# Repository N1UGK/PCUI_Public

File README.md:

# PCUI (Pocket Computer Universal Interface)
This is the official repo for firmware updates for the PCUI, owners manuals, and general information.  Further, this repo contains a collection of programs for various pocket computers and calculators supported by the PCUI.

## Development History

https://n1ugk.com/2025/12/pocket-computer-universal-interface/

## Features Summary

+ Provides cassette interface emulation to read and write programs and data directly to and from a micro SD card.
+ Provides a printer interface between the pocket computer or calculator and most standard “line printers” such as dot matrix, thermal receipt printers, serial, parallel, and Wi-Fi.
+ Supports printing of custom glyphs, including math, scientific and engineering symbols unique to each model.
+ Works independently without a computer and can be powered by a single 18650 lithium ion rechargeable battery.
+ OLED screen with user-friendly menu system and operating modes
+ Interface packs provide connectivity to each supported model, no need for OEM connection cables.
+ Updatable firmware and PC or Mac connectivity via USB for mounting micro SD card
+ Plotter emulation mode to provide printouts of plots using modern printers allowing programs which leveraged plotter features to be used on modern printers.
+ ASCII BASIC conversion to tokenized BASIC “on the fly”, allowing for program edits and program creation on a Mac or PC and directly sending it to a pocket computer.
+ Wi-Fi connectivity and web interface for program viewing, editing, UI control, printing, and status.
+ Online program library browsing and installing directly from GitHub allows you to view community released programs for various models of pocket computers directly from the PCUI.
+ True low-level cassette interface integration - byte level retrieval and storage of programs and data images, not just a simple "record" and "playback" mechanism.
+	3D printed case available with additional “docking station” 3D models for specific pocket computers.
  
## Supported Models

The following models are currently supported with more models in progress:

+ Texas Instruments	Graph Link Graphing Calculators
  + TI-82*, TI-85*, TI-86*, TI-89*, TI-92*, TI-92 Plus*, Voyage 200*
+ Sharp 9-pin “CE-121” / “CE-122” Compatibles
  + PC-1210, PC-1211, PC-1212, TRS-80 PC-1*
+ Sharp	Older 11-pin “CE-126P” Compatibles
  + PC-1245, PC-1246, PC-1246S, PC-1247, PC-1248, Tandy PC-8*
  + PC-1250, PC-1250A, PC-1251, PC-1251H, PC-1255, Tandy PC-3* and PC-3 A/B*, PC-1270
+ 11-pin “CE-126P” Compatibles
  + PC-1260, PC-1280
+ Sharp	Newer 11-pin “CE-126P” Compatibles
  + PC-1401, PC-1403*, PC-1421, PC-1430, PC-1450, EL-5500, EL-5500 II, EL-5500III*
+ Casio	12-pin PB-100 Series FP-12(S) Compatibles
  + PB-100, PB-110, PB-120, PB-200, PB-400, PB-410*, FX-700P, FX-710P, Tandy PC-4 Version B*, TRS-80 PC-4 Version A*
+ Casio	12-pin FX “Clamshell” Series
  + FX-770P, FX-780P, FX-781P, FX-785P, FX-790P, FX-791P, FX-795P, Tandy PC-5*, Tandy PC-6*
+ Casio	15-pin “FA-10” Compatibles
  + PB-700*, PB-770*
+ Casio	FX-702P*, FX-602P*

_*Tested and Verified, others should work since they use the same interface_

The PCUI Owners manual can be found in the [Documentation](./Documentation/) folder.

Firmware updates can be found in the [Firmware](./Firmware/) folder.

## 3D Printed Case

The PCUI has a case which can printed with a 3D printer.  The case STEP files are in the hardware folder.  The case includes all 3D models needed - both the top and bottom halves of the case, the 4 buttons, the two pocket computer connector covers, and the slide switch.

In addition to the PCUI case, there will be several "docking station" style model files as well.  For example, there is a TRS-80 PC-4 / Casio PB-100 series dock available for printing.  The interface pack fits inside of the 3D printed dock, providing a stable platform for connecting the pocket computer to the PCUI.  Similar models will be created for other pocket computers and made available as well.

## 3D Printed "Docks"

Several interface packs have optional "docks" available for providing a more stable connection and better usability.  These are 3D printed and also available here under the Hardware folder if you wish to print them yourself.

## Purchasing a Kit or Fully Assembled PCUI

A PCUI can be purchased as a kit or fully assembled.  

+ PCUI Kit - includes pre-flashed Pico 2 W, Main PCB and all components.  Interface pack kits are add-ons.  
  + Assembly instructions are located in the [Documentation](./Documentation/) folder.
  + The BOM, 3D model, KiCad Projects are located in the [Hardware](./Hardware/) folder.
+ PCUI Fully Assembled - includes a fully assembled PCUI and chosen interface pack add-ons.
+ To purchase a PCUI, <a href="https://www.tindie.com/products/n1ugk/pocket-computer-universal-interface-pcui/">click here</a>.

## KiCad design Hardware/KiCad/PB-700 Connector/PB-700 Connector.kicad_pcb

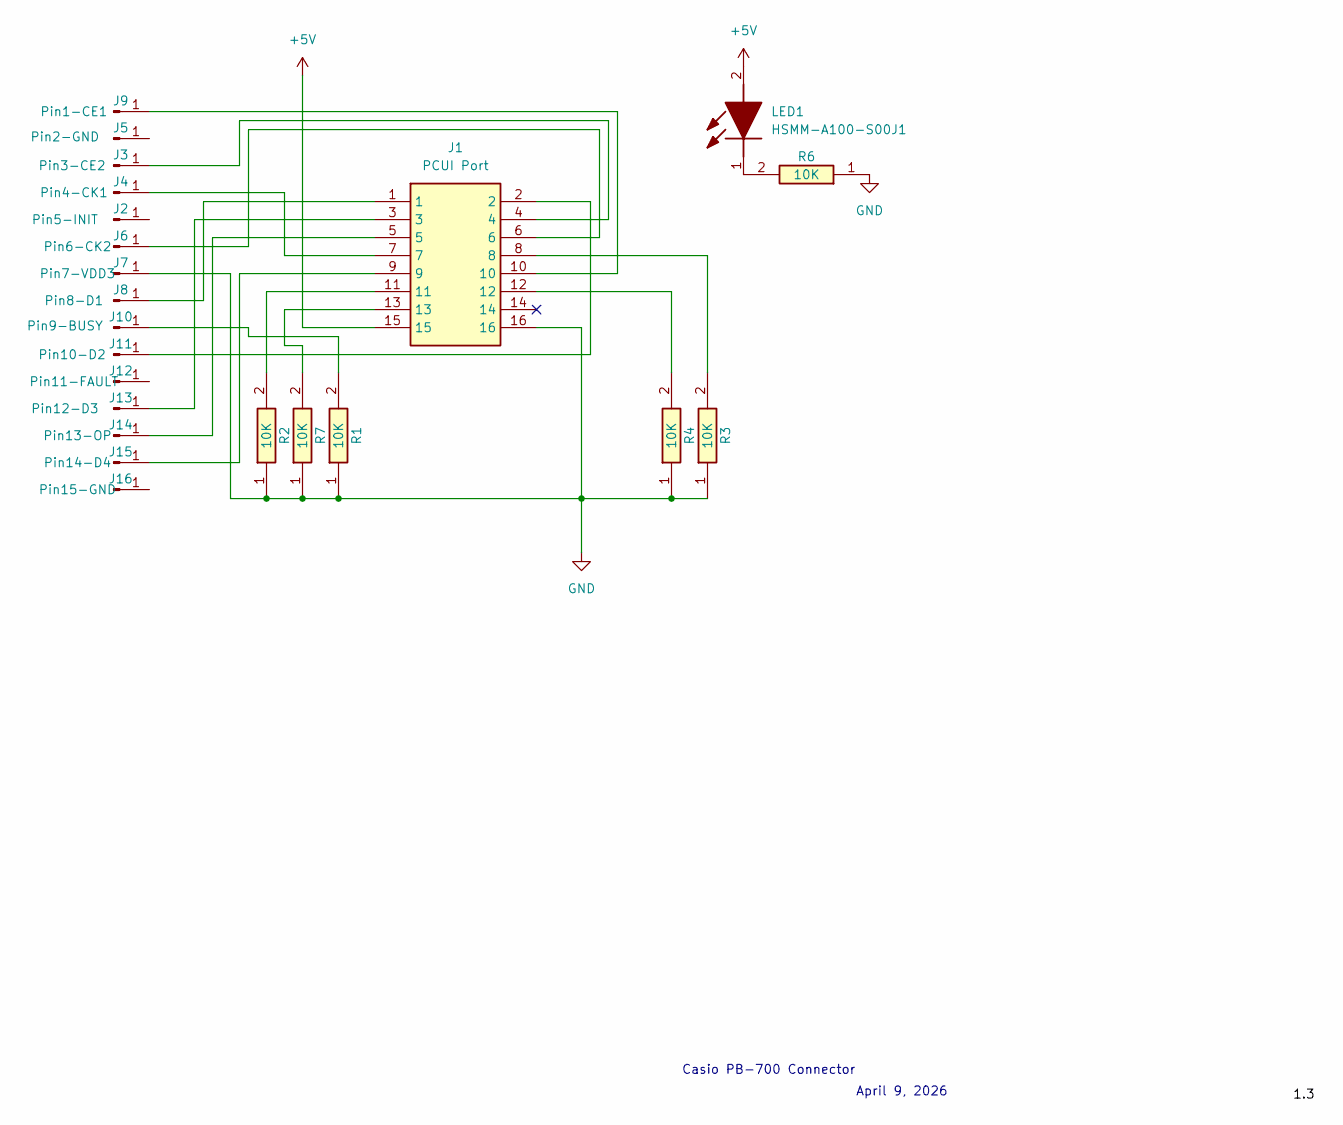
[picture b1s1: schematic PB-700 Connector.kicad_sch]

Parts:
J1: PCUI Port; TSS-108-XX-YYY-D; Manufacturer_Part_Number TSS-108-02-L-D
J2: Pin5-INIT; TH_1mm_1.5mm
J3: Pin3-CE2; TH_1mm_1.5mm
J4: Pin4-CK1; TH_1mm_1.5mm
J5: Pin2-GND; TH_1mm_1.5mm
J6: Pin6-CK2; TH_1mm_1.5mm
J7: Pin7-VDD3; TH_1mm_1.5mm
J8: Pin8-D1; TH_1mm_1.5mm
J9: Pin1-CE1; TH_1mm_1.5mm
J10: Pin9-BUSY; TH_1mm_1.5mm
J11: Pin10-D2; TH_1mm_1.5mm
J12: Pin11-FAULT; TH_1mm_1.5mm
J13: Pin12-D3; TH_1mm_1.5mm
J14: Pin13-OP; TH_1mm_1.5mm
J15: Pin14-D4; TH_1mm_1.5mm
J16: Pin15-GND; TH_1mm_1.5mm
LED1: HSMM-A100-S00J1; LEDM3528X200N; Mouser Part Number 630-HSMM-A100-S00J1
R1, R2, R3, R4, R6, R7: 10K; RESC2013X65N; Mouser Part Number 756-WCR0805-10KFI

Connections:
+5V: J1.15, LED1.2 (A)
GND: J1.16, J7.1, R1.1, R2.1, R3.1, R4.1, R6.1, R7.1
unnamed: J1.8, R3.2
unnamed: J1.11, R2.2
unnamed: J1.12, R4.2
unnamed: J1.13, R7.2
unnamed: J1.4, J3.1
unnamed: J1.7, J4.1
unnamed: J1.6, J6.1
unnamed: J1.1, J8.1
unnamed: J1.10, J9.1
unnamed: J10.1, R1.2
unnamed: J1.2, J11.1
unnamed: J1.3, J13.1
unnamed: J1.5, J14.1
unnamed: J1.9, J15.1
unnamed: LED1.1 (K), R6.2

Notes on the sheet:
April 9, 2026
Casio PB-700 Connector

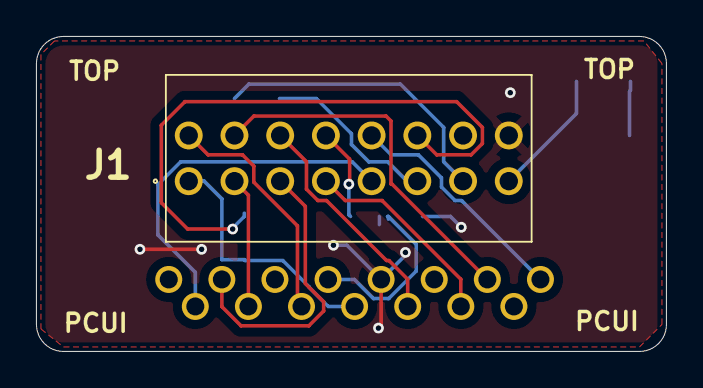
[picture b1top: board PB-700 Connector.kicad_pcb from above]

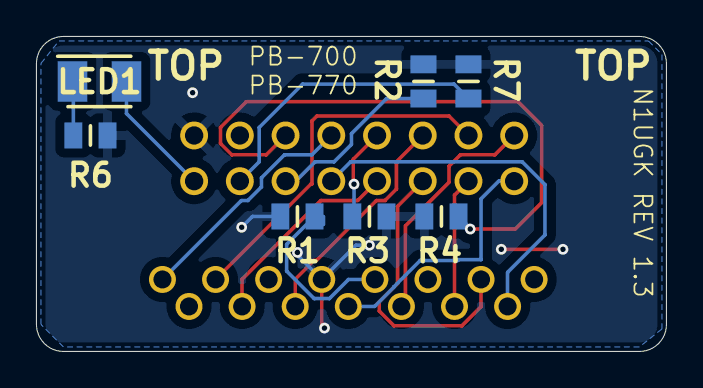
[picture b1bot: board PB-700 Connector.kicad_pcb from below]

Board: 2 copper layers, 35.0 x 17.5 mm, 23 parts (22 on the bottom side), 17 nets.

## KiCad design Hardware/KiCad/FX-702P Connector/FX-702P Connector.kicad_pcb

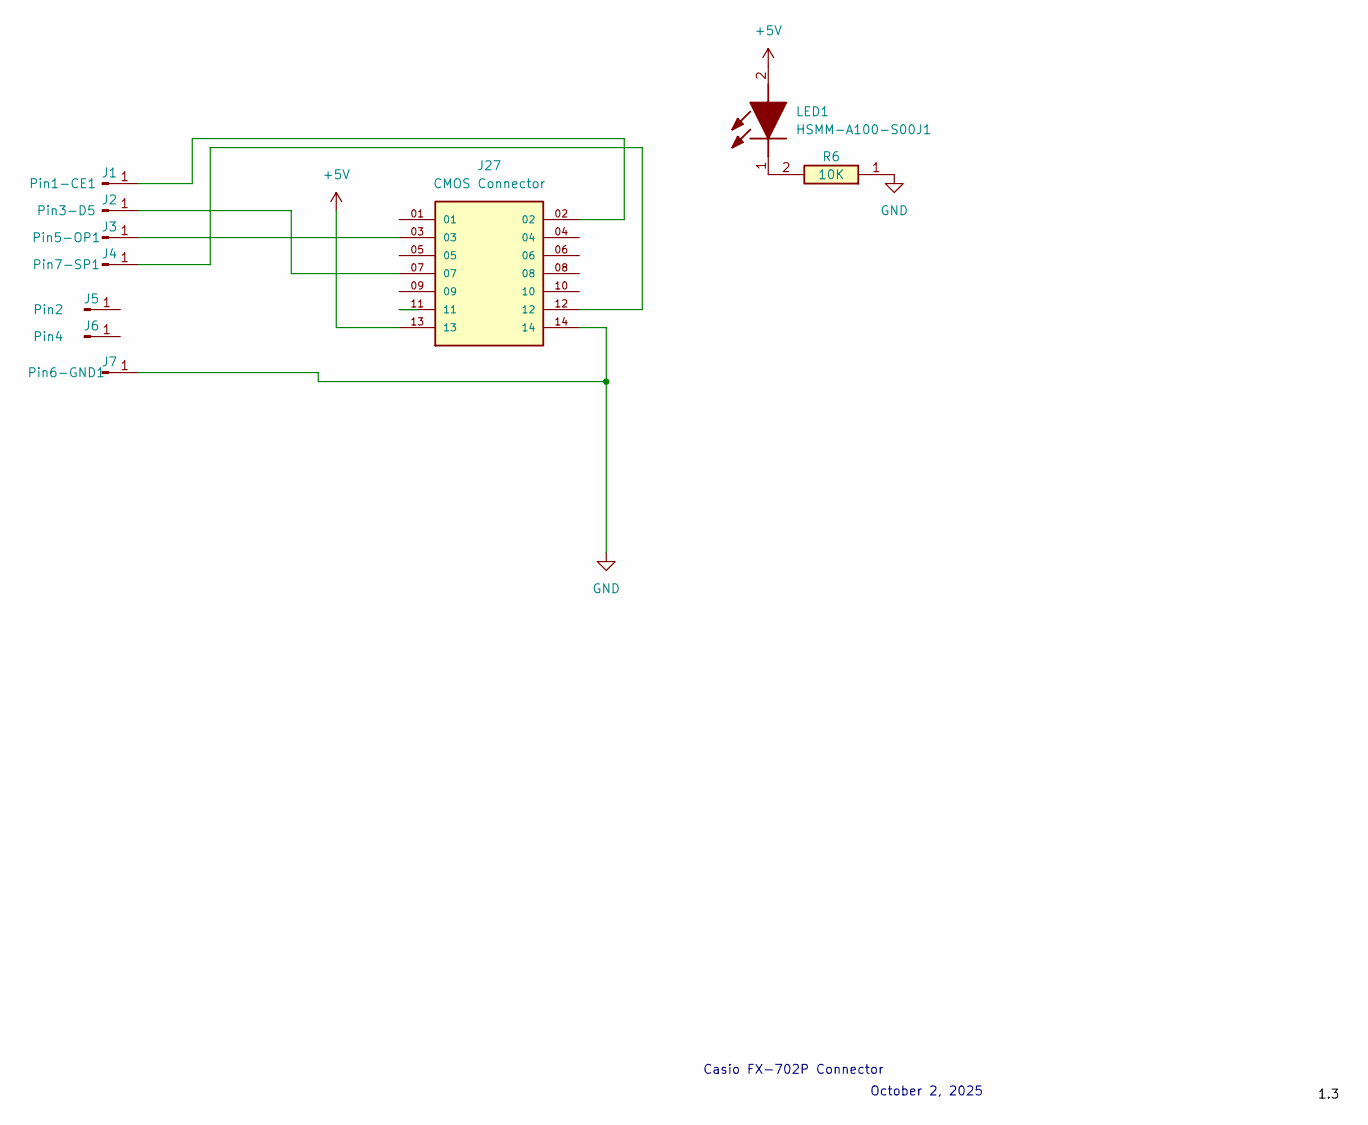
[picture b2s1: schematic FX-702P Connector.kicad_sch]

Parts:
J1: Pin1-CE1; TH_1mm_1.5mm
J2: Pin3-D5; TH_1mm_1.5mm
J3: Pin5-OP1; TH_1mm_1.5mm
J4: Pin7-SP1; TH_1mm_1.5mm
J5: Pin2; TH_1mm_1.5mm
J6: Pin4; TH_1mm_1.5mm
J7: Pin6-GND1; TH_1mm_1.5mm
J27: CMOS Connector; SAMTEC_TSS-107-02-H-D; PARTREV R
LED1: HSMM-A100-S00J1; LEDM3528X200N; Mouser Part Number 630-HSMM-A100-S00J1
R6: 10K; RESC2013X65N; Mouser Part Number 756-WCR0805-10KFI

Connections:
+5V: J27.13, LED1.2 (A)
GND: J7.1, J27.14, R6.1
unnamed: J1.1, J27.02
unnamed: J2.1, J27.07
unnamed: J3.1, J27.03
unnamed: J4.1, J27.12
unnamed: LED1.1 (K), R6.2

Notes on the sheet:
October 2, 2025
Casio FX-702P Connector

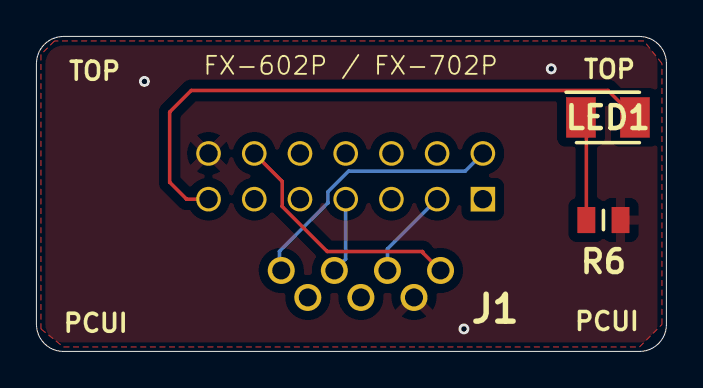
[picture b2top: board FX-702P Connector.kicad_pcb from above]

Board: 2 copper layers, 35.0 x 17.5 mm, 10 parts (1 on the bottom side), 7 nets.

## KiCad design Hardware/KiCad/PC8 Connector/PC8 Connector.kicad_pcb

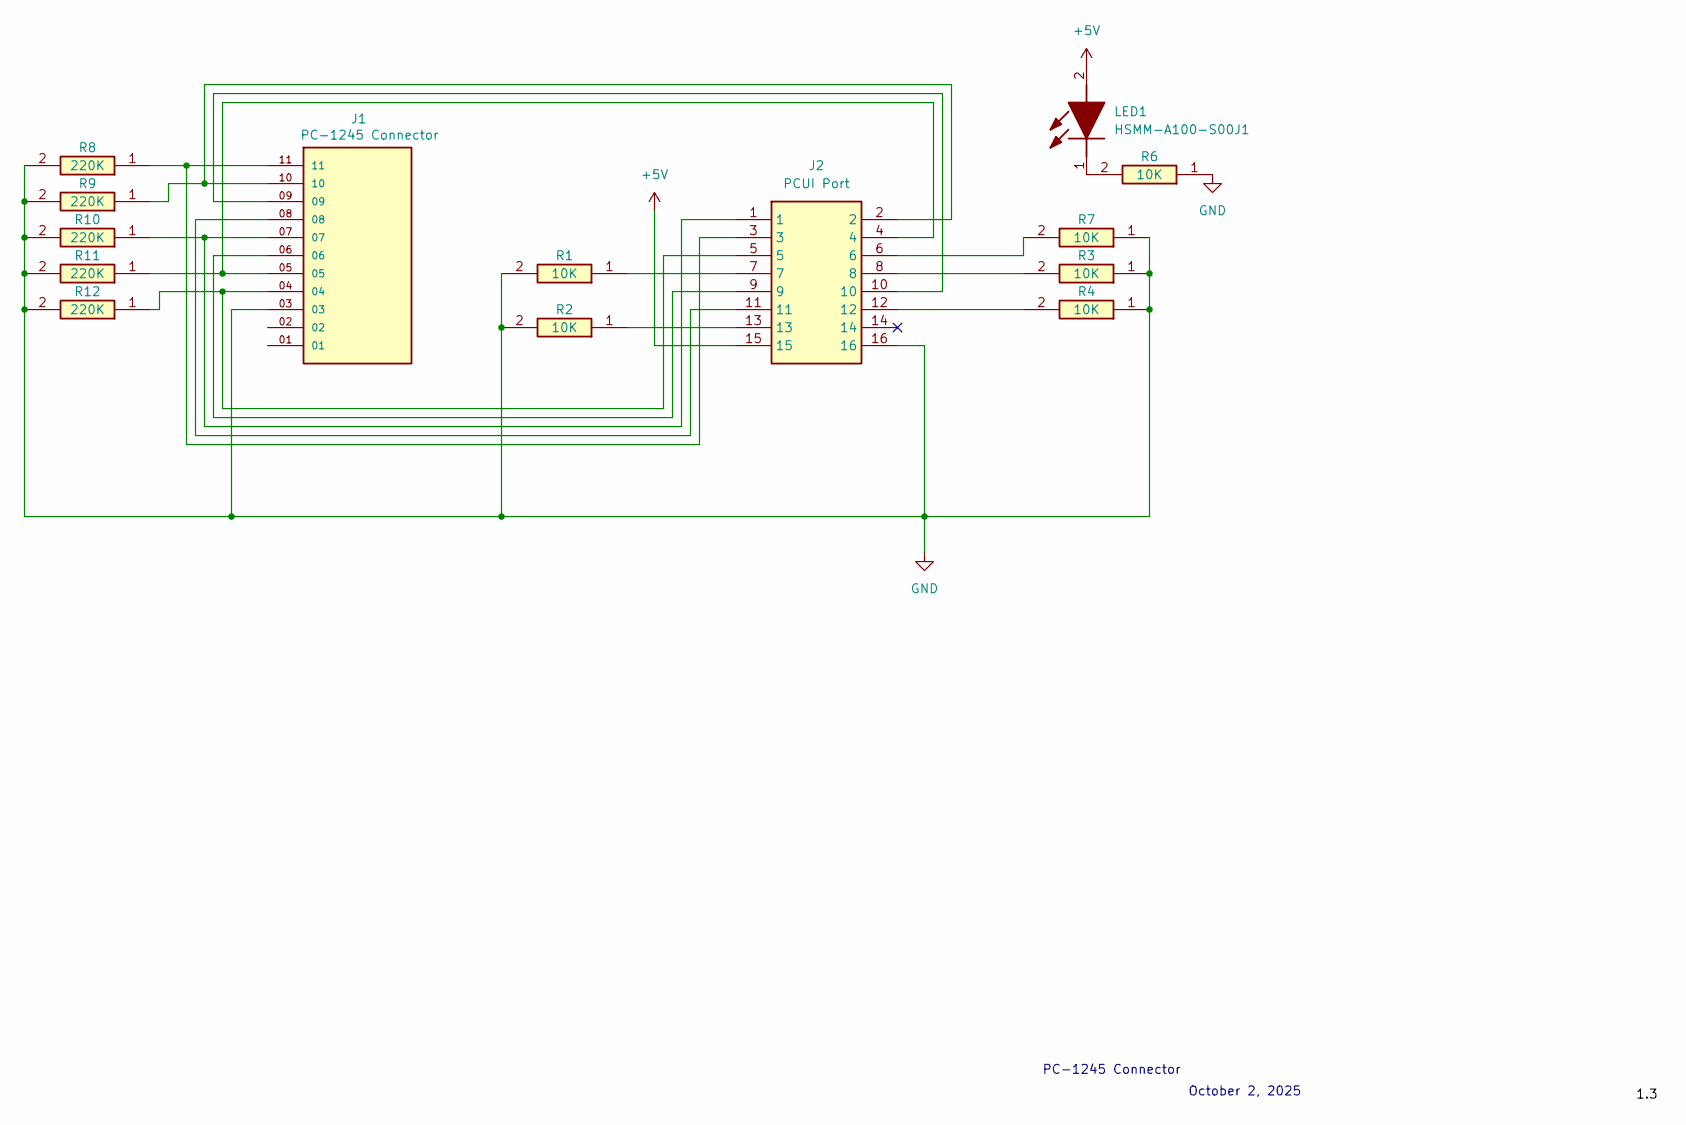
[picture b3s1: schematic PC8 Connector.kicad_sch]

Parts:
J1: PC-1245 Connector; SAMTEC_TSW-111-14-G-S; PARTREV R
J2: PCUI Port; TSS-108-XX-YYY-D; Manufacturer_Part_Number TSS-108-02-L-D
LED1: HSMM-A100-S00J1; LEDM3528X200N; Mouser Part Number 630-HSMM-A100-S00J1
R1, R2, R3, R4, R6, R7: 10K; RESC2013X65N; Mouser Part Number 756-WCR0805-10KFI
R8, R9, R10, R11, R12: 220K; RESC2013X65N; Mouser Part Number 756-WCR0805-10KFI

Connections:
+5V: J2.15, LED1.2 (A); also elsewhere on the board
GND: J1.03, J2.16, R1.2, R2.2, R3.1, R4.1, R6.1, R7.1, R8.2, R9.2, R10.2, R11.2, R12.2
unnamed: J1.04, J2.5, R12.1
unnamed: J1.05, J2.4, R11.1
unnamed: J1.06, J2.9
unnamed: J1.07, J2.1, R10.1
unnamed: J1.08, J2.11
unnamed: J1.09, J2.10
unnamed: J1.10, J2.2, R9.1
unnamed: J1.11, J2.3, R8.1
unnamed: J2.6, R7.2
unnamed: J2.7, R1.1
unnamed: J2.8, R3.2
unnamed: J2.12, R4.2
unnamed: J2.13, R2.1
unnamed 15: LED1.1 (K), R6.2; also elsewhere on the board

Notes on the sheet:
October 2, 2025
PC-1245 Connector

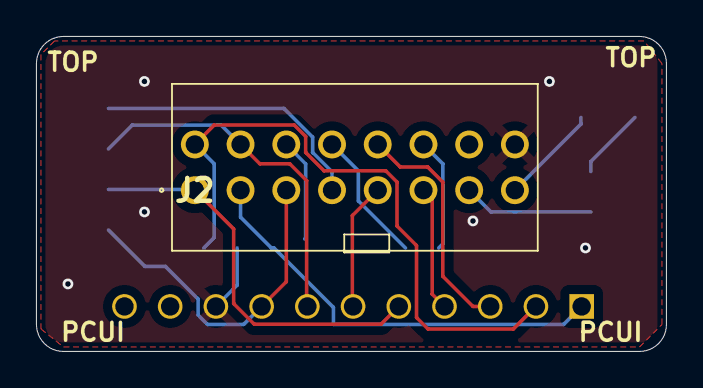
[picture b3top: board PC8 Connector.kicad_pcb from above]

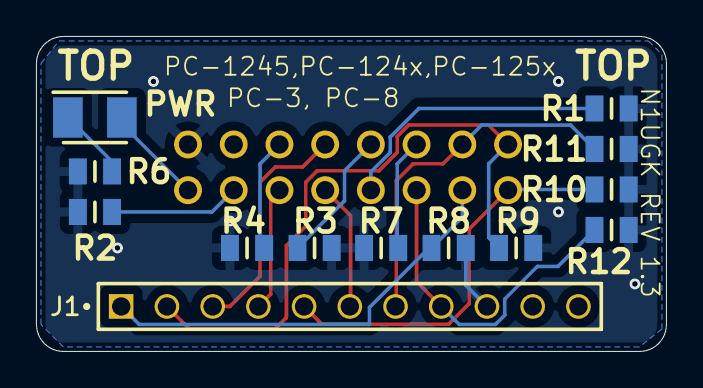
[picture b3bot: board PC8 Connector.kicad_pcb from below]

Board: 2 copper layers, 35.0 x 17.5 mm, 14 parts (13 on the bottom side), 16 nets.

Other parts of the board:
PWR: HSMM-A100-S00J1; LEDM3528X200N

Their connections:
+5V: PWR.2 (A); also elsewhere on the board
unnamed 15: PWR.1 (K); also elsewhere on the board

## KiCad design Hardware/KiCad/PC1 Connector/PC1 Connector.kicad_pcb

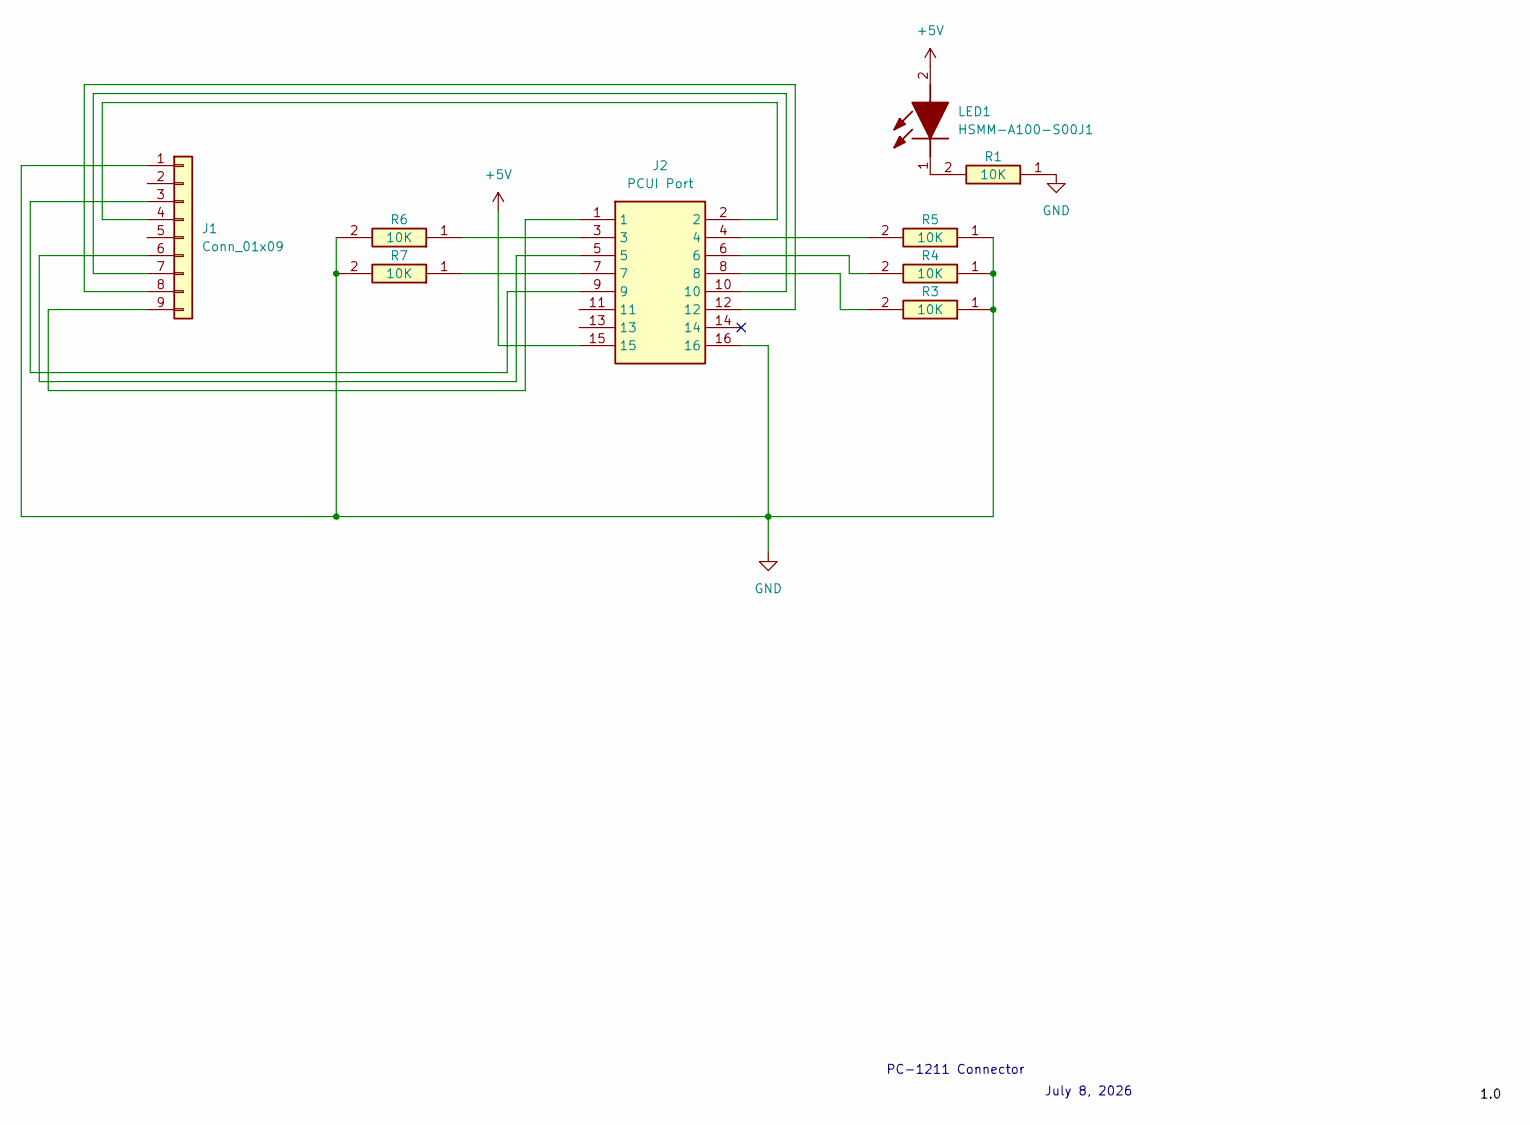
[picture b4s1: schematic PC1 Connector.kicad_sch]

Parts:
J1: Conn_01x09; PinHeader_1x09_P2.54mm_Vertical
J2: PCUI Port; TSS-108-XX-YYY-D; Manufacturer_Part_Number TSS-108-02-L-D
LED1: HSMM-A100-S00J1; LEDM3528X200N; Mouser Part Number 630-HSMM-A100-S00J1
R1, R3, R4, R5, R6, R7: 10K; RESC2013X65N; Mouser Part Number 756-WCR0805-10KFI

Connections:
+5V: J2.15, LED1.2 (A)
GND: J1.1, J2.16, R1.1, R3.1, R4.1, R5.1, R6.2, R7.2
unnamed: J1.3, J2.9
unnamed: J1.4, J2.2
unnamed: J1.6, J2.5
unnamed: J1.7, J2.10
unnamed: J1.8, J2.12
unnamed: J1.9, J2.1
unnamed: J2.3, R6.1
unnamed: J2.4, R5.2
unnamed: J2.6, R4.2
unnamed: J2.7, R7.1
unnamed: J2.8, R3.2
unnamed: LED1.1 (K), R1.2

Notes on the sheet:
July 8, 2026
PC-1211 Connector

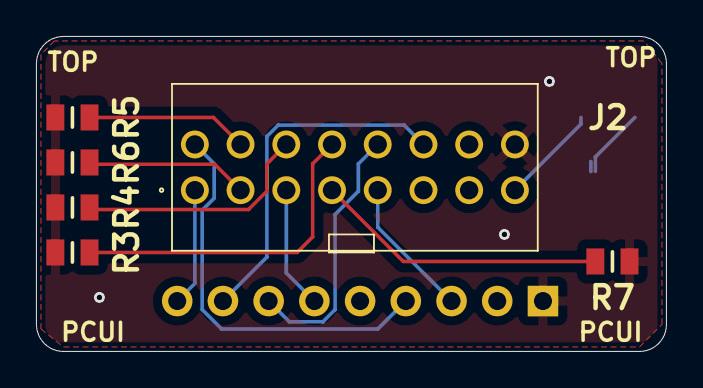
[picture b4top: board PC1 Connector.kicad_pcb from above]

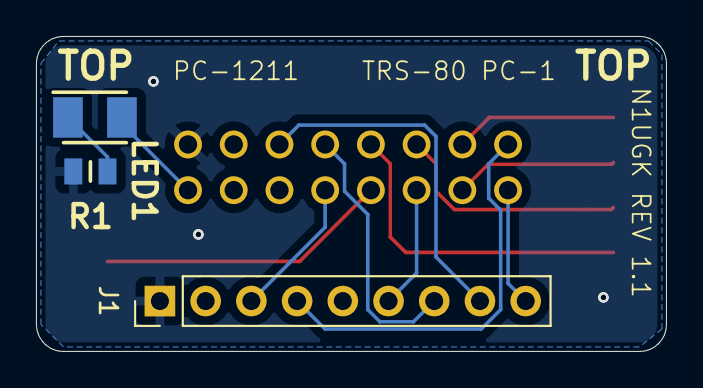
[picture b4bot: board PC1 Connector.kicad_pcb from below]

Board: 2 copper layers, 35.0 x 17.5 mm, 9 parts (3 on the bottom side), 14 nets.
